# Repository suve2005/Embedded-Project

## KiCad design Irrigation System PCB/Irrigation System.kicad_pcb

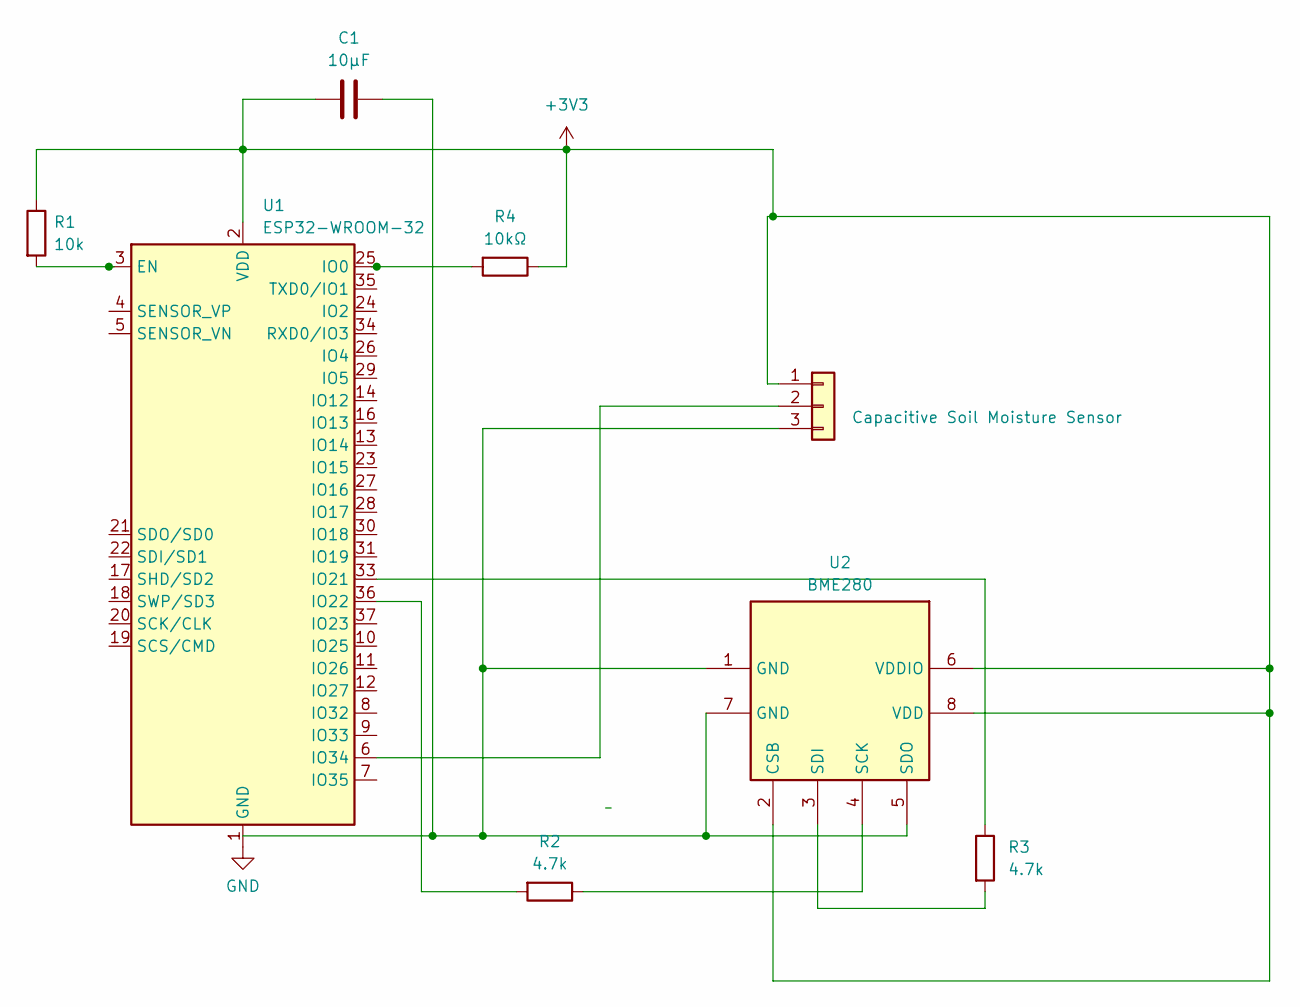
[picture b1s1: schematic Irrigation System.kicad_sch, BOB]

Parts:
C1: 10µF; CP_Radial_D5.0mm_P2.50mm
J1: Capacitive Soil Moisture Sensor; PinHeader_1x03_P2.54mm_Vertical
R1: 10k; R_Axial_DIN0207_L6.3mm_D2.5mm_P10.16mm_Horizontal
R2, R3: 4.7k; R_Axial_DIN0207_L6.3mm_D2.5mm_P10.16mm_Horizontal
R4: 10kΩ; R_Axial_DIN0207_L6.3mm_D2.5mm_P10.16mm_Horizontal
U1: ESP32-WROOM-32
U2: BME280; Bosch_LGA-8_2.5x2.5mm_P0.65mm_ClockwisePinNumbering

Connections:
+3V3: C1.2, J1.1, R1.1, R4.1, U1.2 (VDD), U2.2 (CSB), U2.6 (VDDIO), U2.8 (VDD)
GND: U1.1 (GND), U1.15 (GND), U1.38 (GND), U1.39 (GND)
unnamed: J1.2, U1.6 (IO34)
unnamed: C1.1, J1.3, U2.1 (GND), U2.5 (SDO), U2.7 (GND)
unnamed: R1.2, U1.3 (EN)
unnamed: R4.2, U1.25 (IO0)
unnamed: R3.1, U1.33 (IO21)
unnamed: R2.2, U1.36 (IO22)
unnamed: R2.1, U2.4 (SCK)
unnamed: R3.2, U2.3 (SDI)

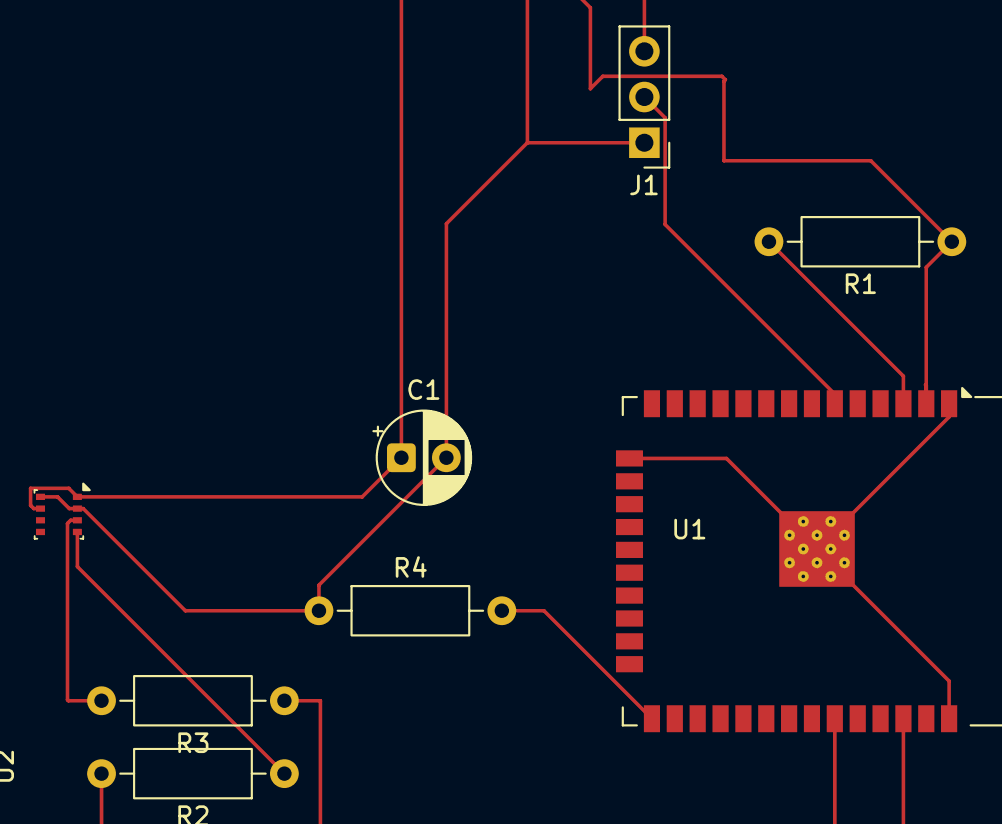
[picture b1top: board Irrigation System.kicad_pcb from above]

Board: 2 copper layers, 8 parts (0 on the bottom side), 10 nets.
